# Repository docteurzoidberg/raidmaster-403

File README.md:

# Raidmaster 403

Tripmaster GPS de rallye-raid fait maison pour une **Peugeot 403 break Familiale de 1961**, pensé pour le raid
**Crazy Dust 2027** et utilisable au quotidien en mode balade. Boîtier autonome aimanté sur la tôle du
tableau de bord : distances partielles A et B, odomètre, vitesse, cap, moyenne, chrono.

Site du projet : **<https://docteurzoidberg.github.io/raidmaster-403/>** (présentation, maquette 3D, simulateur
dans le navigateur, manuel d'utilisation en cours de rédaction).

<p align="center"><sub>Simulateur PC, échelle 1:1 de l'écran 480 × 320. GIF régénéré automatiquement à chaque build qui change l'interface.</sub></p>

## Matériel

| Élément | Choix |
|---|---|
| Carte | [Waveshare ESP32-S3-Touch-LCD-3.5B](https://www.waveshare.com/wiki/ESP32-S3-Touch-LCD-3.5B) : ESP32-S3, 8 Mo PSRAM, 16 Mo flash |
| Écran | 3,5" IPS 480 × 320, AXS15231B en QSPI, tactile capacitif intégré |
| GPS | au choix au montage : u-blox NEO-M9N sur la carte fille (UART, 10 Hz) + antenne active déportée sous le pare-brise, ou module externe NEO-M8N + boussole (« puck » de drone) posé sur le tableau de bord |
| Cap | magnétomètre QMC5883L (I²C) |
| Alimentation | batterie Li-ion interne gérée par l'AXP2101, recharge USB-C, aucun fil 12 V |
| Commandes | 5 boutons (A, B, menu, ▲ haut / +, ▼ bas / −) + tactile |
| Boîtier | PETG / ASA imprimé (pas de PLA : habitacle à 60 °C en été) ; fixation sur la tôle à définir (plus d'aimants noyés dans le boîtier ; des aimants rapportés au dos restent possibles) |

Distance **GPS uniquement**, sans capteur de roue ni intervention sur le câblage de la voiture.

## État

| Étape | Contenu | État |
|---|---|---|
| 1 | Squelette CMake + simulateur SDL 480 × 320 | fait |
| 2 | Core portable + tests : `gps_parser` (NMEA, sur minmea), `trip_engine` (distance, moyenne, chrono, calibration), `app` (boutons, menu, sauvegarde) | fait |
| 3 | Interface LVGL câblée sur le core : raid, balade, menu réglages actif, calibration auto, démarrage animé, mode nuit | fait |
| 4 | Simulateur : rejeu de traces NMEA, trajet simulé, scénarios de bout en bout | 23 scénarios en place (GPS, puck débranché, calibration de la boussole) ; simulateur web dans le navigateur (WebAssembly, maquette 3D et carte) ; inclinomètre et matériel à venir |
| 5-6 | HAL ESP32 et firmware sur la carte | en cours : firmware de démo validé sur la carte (écran, tactile, core et UI du sim, trajet GPS simulé, NVS, heure de la RTC, état USB / batterie), jingle de démarrage par le codec ES8311 (à écouter sur la carte) ; pilote du récepteur GPS réel écrit (NEO-M9N ou puck NEO-M8N sur UART : débit trouvé, modèle reconnu, réglé à 10 Hz) et de sa boussole (QMC5883L, IST8310, HMC5883L ou LIS3MDL sur I²C, cap dans le journal), à essayer sur la carte ; cap à l'écran, boutons, charge de la batterie à venir |
| 7-13 | Essai en modules, carte fille 4 couches (GPS, magnétomètre), boîtier aimanté, essai raid | à faire ; carte 3.5B reçue, datasheets et modèle 3D rassemblés ; PCB placé, non routé (version 1.1 : GPS interne ou puck externe) ; maquette 3D des cartes dans un boîtier de principe validée ([en ligne](https://docteurzoidberg.github.io/raidmaster-403/mockup/)) ; boîtier dessiné dans Fusion, STEP des pièces dans `enclosure/stepfiles/`, à éprouver |

Pas encore là : compensation d'inclinaison de la boussole, réglages de charge de la batterie (l'état
USB / batterie est lu, pas configuré), température réelle, log GPX.

## Maquette 3D

Les trois cartes (Waveshare, carte fille GPS et magnétomètre, carte boutons) dans leur boîtier (aspect
retenu : cannelures, pare-chocs en TPU, liseré et lettrage), assemblé ou éclaté, à faire tourner dans le navigateur : **<https://docteurzoidberg.github.io/raidmaster-403/mockup/>**. Sources de la page
dans [`web/mockup/`](web/mockup/) ; modèles 3D externes et fichiers STEP du boîtier dessiné dans Fusion (pièces
à éprouver) dans [`enclosure/`](enclosure/README.md).

<p align="center"><sub>Rendus Blender de la maquette : boîtier de 123 × 94 × 33 mm avec l'aspect retenu, esquisse du modèle dessiné pour l'impression.</sub></p>

## Simulateur dans le navigateur

Le firmware (mêmes `core/` et `ui/`, compilés en WebAssembly) tourne dans la maquette 3D : l'écran est
vivant, les cinq capuchons se cliquent (appui long en gardant le doigt 0,6 s), et une carte OpenStreetMap
suit le trajet GPS rejoué : **<https://docteurzoidberg.github.io/raidmaster-403/sim/>** (menu de toutes les
pages du site). Trajets : les scénarios des tests, ou un fichier NMEA à glisser sur la page
(il reste dans le navigateur) ; vitesse ×1 à ×1000 ; la case « Jouer les actions et les vérifications »
rejoue les appuis du scénario et affiche ses vérifications en vert ou rouge. Trips et réglages restent dans
le navigateur (bouton « Remise à zéro »). Son coupé par défaut (bouton « Son »). Mêmes touches que le
simulateur PC. Le tripmaster s'affiche de face (bouton « Recentrer » après une rotation) ; le bouton « Écran
seul » montre l'écran sur toute la largeur, avec une barre des cinq boutons dessous (`?vue=2d` l'ouvre
directement). Sur la carte, « Centrer » garde le véhicule au centre (un glisser le coupe).

Construit en local et commité dans `web/sim/` (publié avec le site). Prérequis :
[emsdk](https://emscripten.org/docs/getting_started/downloads.html) installé dans `~/sdk/emsdk` (ou
`EMSDK_DIR`), Node (celui d'emsdk suffit).

```bash
cd software
tools/web.sh             # build (build-web/), test sous Node, copie dans web/sim/
tools/web.sh serve       # sert le site web/ : http://localhost:8000/ (accueil), …/sim/
```

`tools/web.sh build`, `test` et `copy` font chaque étape seule. Le test joue les 23 scénarios dans le
module WebAssembly avec leurs vérifications, et compare une capture de l'écran à celle du simulateur PC
(identique au pixel près).

## Cartes électroniques

Deux circuits fabriqués d'un seul tenant puis séparés : la **carte fille** (78 × 54 mm, 4 couches), enfichée
au dos de la Waveshare, existe en deux variantes choisies au soudage : **GPS interne** (NEO-M9N, prise
d'antenne U.FL et boussole) ou **puck externe** (prise JST-PH 6 broches au bord gauche, protection et tampon
I²C pour le branchement à chaud) ; la **carte boutons**
(108 × 20 mm), vissée derrière la façade, porte les 5 poussoirs, les 2 voyants et deux expandeurs I²C, et
rejoint la carte fille par une nappe souple de 6 voies. Tout se soude au fer.

<p align="center"><sub>Rendus du visualiseur 3D de KiCad, dessus (côté batterie) et dessous (côté écran) : composants placés, routage à venir.</sub></p>

## Démarrage rapide (simulateur PC)

Prérequis : CMake ≥ 3.20, Ninja, un compilateur C11, SDL2 (`sudo apt install libsdl2-dev` sous
Debian / Ubuntu / WSL). LVGL, Unity et les autres dépendances sont téléchargées par CMake ou déjà dans le
dépôt. Le code est dans `software/` : les commandes se lancent depuis ce dossier.

```bash
cd software
cmake --preset sim
cmake --build build-sim
./build-sim/raidmaster-sim                                    # trajet simulé
./build-sim/raidmaster-sim --replay trace.nmea --speed 10     # rejoue un fichier NMEA ×10
```

Le core tourne comme sur la carte : GPS fourni par le simulateur (trajet simulé ou fichier rejoué),
réglages et distances sauvegardés dans `sim-storage.json`. Au lancement, le jingle de démarrage se joue
avec l'animation par la sortie audio SDL (WSLg sous WSL) ; `SDL_AUDIODRIVER=dummy` le coupe.

| Option | Effet |
|---|---|
| `--replay fichier.nmea` | rejoue un fichier au rythme de ses horodatages (sinon trajet simulé : boucle de 2 min) |
| `--speed N` | accélère le temps GPS, 1 à 1000 |
| `--loop` | rejoue le fichier en boucle |
| `--storage f.json` / `--no-storage` | fichier de sauvegarde (défaut `./sim-storage.json`) / en mémoire |
| `--script actions.txt --out dossier` | joue des actions horodatées en temps virtuel, sans attente (tests de bout en bout) |

| Touche | Bouton / action |
|---|---|
| `a` / `b` | A / B : RAZ Trip A / Trip B ; à la calibration auto : départ et arrivée (A), annuler (B) |
| `+` / `−` | ±10 m sur le trip actif ; dans le menu : monter / descendre, ou changer la valeur en édition |
| `m` | trip actif A ↔ B ; dans le menu : choisir / valider |
| `Maj` + touche | appui long : `Maj`+`m` entre dans le menu ou en sort, `Maj`+`+`/`−` ±100 m |
| `n` ou `Tab` | bascule jour / nuit |
| `d` | coupe / rétablit le signal GPS (tunnel) |
| `g` | débranche / rebranche le récepteur GPS (« GPS × », puis recherche du débit et réglage) |
| `c` | débranche / rebranche la boussole |
| `r` | la voiture tourne sur place / s'arrête (calibration de la boussole) |
| `p` | alimentation suivante (barre d'état) : batterie 68 %, USB en charge, USB batterie pleine, USB sans batterie, batterie 8 % |
| `v` | écran suivant (debug) |
| `Échap` | quitter (sauvegarde) |

### Tests

```bash
cd software
ctest --preset sim
tools/check.sh        # build + avertissements + tests + GIF + build firmware + simulateur web, résumé court
                      # (-c : tout recompiler, -s : sim seul, -w : sans le web)
```

- Tests unitaires du core avec [Unity](https://github.com/ThrowTheSwitch/Unity) : parseur NMEA, moteur
  de distance, application (boutons, menu, sauvegarde, source du cap), liaison avec le récepteur u-blox,
  boussole, synthétiseur et jingle de démarrage.
- Scénarios de bout en bout (`software/tests/fixtures/scenarios/`, 23 au catalogue) : le simulateur sans fenêtre
  rejoue une trace, appuie sur les boutons et vérifie l'état, en temps virtuel (une étape de 12 h se
  joue en moins d'une seconde, la suite entière en ~1,5 s). Les traces sont générées au build depuis
  l'itinéraire `route.txt` de chaque scénario (`software/tests/tools/gen_route.py`, Python sans dépendance).
- Les traces NMEA longues de `software/references/traces-brutes/` ne sont pas versionnées : présentes, elles sont
  rejouées (distances à ±0,1 % de la référence) ; absentes, ces tests sont ignorés.

### GIF de démo

`docs/demo/raidmaster-demo.gif` est régénéré par la cible CMake `demo_gif` à chaque build où le binaire du
simulateur change. Le simulateur tourne alors sans fenêtre, en temps virtuel, et enchaîne démarrage, raid,
balade, menu, calibration et raid de nuit. Le GIF se commite avec la modification d'interface qui l'a
produit.

- Désactiver : `cmake --preset sim -DRAIDMASTER_DEMO_GIF=OFF`.
- À la demande, agrandi ou vers un autre fichier : `software/tools/demo_gif.sh [-s 1..4] [-o sortie.gif]`.

### Animation de démarrage

La 403 fait un tour sur une grille cyan lumineuse, calé sur le jingle : elle s'élance sur les arpèges
puis ralentit en roue libre et s'arrête avec la fin de l'accord. L'animation est rendue dans **Blender**
(36 images en 480 × 320), puis convertie au build en `boot_anim.bin` (palette 256 couleurs) par
`ui/assets/boot_anim/build_boot_anim.py`. Deux formats, mêmes pixels, à trancher : **2** par défaut
(chaque image codée par différence avec la précédente, 0,95 Mo) ou **1** (images brutes, 5,5 Mo), choisi
par l'option CMake `RAIDMASTER_BOOT_ANIM_FORMAT`. Cette conversion demande Python avec Pillow et numpy,
désigné par la variable CMake `RAIDMASTER_PYTHON`.

La scène Blender et les images rendues ne sont pas publiées : elles reposent sur un modèle 3D de la 403
sous licence. Sans elles, ou sans Python, le build passe et l'écran de démarrage affiche une silhouette
fixe.

### Son

Le jingle de démarrage « Grille néon » (arpèges la m · fa · sol puis accord de La majeur, ~2,9 s) est
synthétisé à la volée par `core/synth.c` à partir d'une table de notes (`core/jingles.c`), en PCM 16 bits
mono à 22 050 Hz, sans fichier audio. Sortie SDL sur le sim, codec ES8311 et ampli NS4150B sur la carte
(volume dans `tools/fw.sh menuconfig`).

### Version

Le numéro de version est dans `software/VERSION` (seule source). L'écran de démarrage l'affiche avec la
plateforme : `v0.1.0 · SIM` sur le sim, `v0.1.0 · ESP32 · fe63e9e` sur la carte (hash git du firmware,
suivi de `*` s'il a été compilé avec des modifications non commitées). ESP-IDF reprend le même numéro.

### Polices

Tout l'affichage est en **Share Tech Mono**, compilée en polices bitmap LVGL, uniquement pour les tailles
et les glyphes utilisés. Les mêmes fichiers servent au simulateur et à l'ESP32. Régénération :
`ui/fonts/gen_fonts.sh` (demande Node.js, appelle `lv_font_conv`).

## Participer au projet : partir de zéro

Le développement se fait sur PC, sans la carte : simulateur et tests suffisent jusqu'à l'étape 5.
Testé sous Ubuntu 24.04 (natif ou WSL2).

1. **Outils système**

   ```bash
   sudo apt install build-essential cmake ninja-build git pkg-config libsdl2-dev python3-venv
   ```

   CMake ≥ 3.20. Sous WSL2, la fenêtre SDL s'affiche via WSLg (Windows 11).

2. **Cloner**

   ```bash
   git clone git@github.com:docteurzoidberg/raidmaster-403.git
   cd raidmaster-403
   ```

3. **Python + Pillow + numpy** (optionnel, pour l'animation de démarrage)

   ```bash
   python3 -m venv .venv
   .venv/bin/pip install pillow numpy
   ```

   CMake prend `.venv/` à la racine du dépôt (à côté de `software/`) s'il existe, sinon le `python3` du système. Pour en
   imposer un autre : `-DRAIDMASTER_PYTHON=/chemin/vers/python`. Sans Pillow ou numpy, le build passe
   quand même : le démarrage affiche une silhouette fixe.

4. **Configurer, compiler, tester, lancer**

   ```bash
   cd software
   cmake --preset sim          # télécharge LVGL et Unity au premier passage (connexion requise)
   cmake --build build-sim
   ctest --preset sim
   ./build-sim/raidmaster-sim
   ```

   Le build régénère aussi `docs/demo/raidmaster-demo.gif`. Si tu ne touches pas à l'interface et que
   `git status` le montre modifié, annule-le (`git checkout docs/demo/raidmaster-demo.gif`) ou configure
   avec `-DRAIDMASTER_DEMO_GIF=OFF`.

5. **Traces NMEA de test** (optionnel). `software/references/` n'est pas versionné. Les traces longues se
   génèrent avec les scripts Python de `software/tests/tools/` (sans dépendance, voir `software/tests/tools/README.md`),
   par exemple :

   ```bash
   mkdir -p software/references/traces-brutes
   python3 software/tests/tools/gen_nmea.py --mode linear --duration 3600 --rate 10 --speed-kmh 90 \
       --heading-deg 90 --start-lat 48.8566 --start-lon 2.3522 --start-utc 2026-10-09T06:00:00+00:00 \
       --out software/references/traces-brutes/stage_highway_1h.nmea
   ```

   Sans elles, les tests qui les rejouent sont ignorés. Si les paramètres diffèrent de ceux de
   référence, ces tests peuvent échouer sur les comptes attendus.

6. **Avant de proposer une modification**
   - Pour un changement important, ouvrir d'abord une issue pour en discuter.
   - C11 strict, compilation sans avertissement (`-Wall -Wextra -Wpedantic`), `core/` sans aucun
     accès matériel ni LVGL.
   - Une branche par sujet, `software/tools/check.sh` propre (aucun avertissement, tests verts), GIF de démo commité avec toute modification de
     l'interface, ce README mis à jour s'il devient faux.
   - Optionnel : `compile_commands.json` est exporté dans `software/build-sim/` pour clangd ou ton IDE (lien
     symbolique à la racine si besoin).
   - Code sous GPL-3.0.

## Firmware ESP32

Projet ESP-IDF dans `software/firmware/`, construit avec **ESP-IDF v5.5.6** et les **mêmes** `core/` et
`ui/` que le simulateur (leurs `CMakeLists.txt` servent aux deux builds) ; les pilotes de la carte sont
dans `software/hal_esp32/`. Version actuelle : **démo** sans périphérique externe (trajet GPS simulé,
tactile en guise de boutons, sauvegarde en NVS, animation de démarrage en flash, jingle de démarrage par
le codec ES8311, heure de la RTC, état USB / batterie lu sur le PMIC).

```bash
cd software
tools/fw.sh build        # compile (ESP-IDF chargé par le script)
tools/fw.sh flash        # programme + animation de démarrage, puis 10 s de journal de la carte
tools/fw.sh log 20       # redémarre la carte et affiche 20 s de journal
tools/fw.sh menuconfig   # menu « Raidmaster 403 » : sens de l'écran, rétroéclairage, volume, tactile-boutons, source GPS, boussole
```

Installation d'ESP-IDF, liaison de la carte à WSL (usbipd), réglages et dépannage :
[`software/firmware/README.md`](software/firmware/README.md).

## Organisation du dépôt

```
software/        tout le code ; CMakeLists.txt et CMakePresets.json, build dans software/build-sim/ ;
                 VERSION : numéro de version
  core/          logique métier en C11 portable (aucun accès matériel) : gps_parser, trip_engine, app,
                 gps_synth (trajet simulé), ubx et gps_link (liaison avec un récepteur u-blox), mag (boussole),
                 synth et jingles (son) ; core/include/hal/ : interfaces matériel ;
                 core/third_party/minmea
  ui/            interface LVGL v9 : écrans, thème jour / nuit, polices, images, animation de démarrage
  sim/           simulateur PC SDL2 : fenêtre, clavier, options, mode script (script.c), captures, GIF
  hal_sim/       HAL du simulateur : GPS (rejeu, trajet simulé), stockage JSON, horloge, assets, son SDL
  simweb/        simulateur web (WebAssembly) : front-end, index des scénarios, test Node (tests/)
  hal_simweb/    HAL du simulateur web : stockage du navigateur, son Web Audio (le reste vient de hal_sim/)
  hal_esp32/     HAL et pilotes de la carte (écran QSPI, tactile, RTC, PMIC, son ES8311, NVS, GPS de démo ou réel…),
                 composant ESP-IDF
  firmware/      projet ESP-IDF (main/, sdkconfig.defaults, partitions.csv), build dans software/build-firmware/
  cmake/         modules CMake communs au sim et au firmware (animation de démarrage, version)
  tests/         tests unitaires Unity, scénarios (fixtures/scenarios/), tools/ : outils Python NMEA
  tools/         scripts : check.sh (vérification complète), fw.sh (firmware), web.sh (simulateur web), demo_gif.sh
  references/    non versionné : traces NMEA de test
hardware/kicad/carte-fille/
                 projet KiCad 10 de la carte fille et de la carte boutons (schémas, PCB, bibliothèques,
                 3d/ : modèles 3D propres et leur provenance, export/ : STEP des deux cartes)
hardware/kicad/BOM.md
                 composants des deux cartes : version GPS intégré et version puck GPS externe
enclosure/       boîtier : modèles 3D externes utilisés (README.md), stepfiles/ : exports STEP des pièces du boîtier
web/             site publié sur GitHub Pages : accueil (index.html), common/ : en-tête et styles communs,
                 mockup/ : maquette 3D des cartes dans leur boîtier (page three.js et modèle GLB),
                 sim/ : simulateur web (page, module construit par tools/web.sh, scénarios),
                 manual/ : manuel d'utilisation (en cours de rédaction), img/ : images de l'accueil
.github/         workflow de publication de web/ sur GitHub Pages
docs/demo/       GIF de démo, rendus des cartes (KiCad) et du boîtier (Blender)
```

## Documentation

- [`software/firmware/README.md`](software/firmware/README.md) : installation d'ESP-IDF, liaison de la
  carte, réglages et dépannage du firmware.
- [`software/tests/tools/README.md`](software/tests/tools/README.md) : outils NMEA (génération, bruit,
  validation, enregistrement).
- [`software/tests/fixtures/scenarios/README.md`](software/tests/fixtures/scenarios/README.md) : catalogue
  des scénarios de bout en bout.
- [`enclosure/README.md`](enclosure/README.md) : modèles 3D externes et fichiers STEP du boîtier.
- [`web/README.md`](web/README.md) : le site ([en ligne](https://docteurzoidberg.github.io/raidmaster-403/)) :
  accueil, maquette 3D, simulateur web, manuel.

## Licence

[GPL-3.0](LICENSE).

Composants tiers :

| Composant | Licence | Usage |
|---|---|---|
| [LVGL](https://lvgl.io) v9.2.2 | MIT | interface, téléchargé au build (FetchContent pour le sim, registre ESP-IDF pour le firmware) |
| [ESP-IDF](https://github.com/espressif/esp-idf) v5.5.6 | Apache-2.0 | framework du firmware, installé à part |
| [esp_lcd_axs15231b](https://components.espressif.com/components/espressif/esp_lcd_axs15231b) 1.0.1, [esp_io_expander_tca9554](https://components.espressif.com/components/espressif/esp_io_expander_tca9554) 2.0.3 | Apache-2.0 | pilotes d'écran et d'expandeur, téléchargés au build |
| [esp_codec_dev](https://components.espressif.com/components/espressif/esp_codec_dev) 1.3.4 | Apache-2.0 | pilote du codec audio ES8311, téléchargé au build |
| Séquence d'init du panneau ([exemples Waveshare](https://github.com/waveshareteam/ESP32-S3-Touch-LCD-3.5B)) | Apache-2.0 | dans `hal_esp32/board_display.c` |
| [minmea](https://github.com/kosma/minmea) | MIT (au choix WTFPL / MIT / LGPL-3) | décodage NMEA, dans `core/third_party/minmea/` |
| [Unity](https://github.com/ThrowTheSwitch/Unity) v2.6.1 | MIT | tests, téléchargé au build |
| [Share Tech Mono](https://fonts.google.com/specimen/Share+Tech+Mono) | SIL OFL 1.1 | police, dans `ui/assets/` |
| [three.js](https://threejs.org) 0.186.1 | MIT | maquette 3D et simulateur web (`web/`), chargé depuis jsDelivr |
| [Leaflet](https://leafletjs.com) 1.9.4 | BSD-2-Clause | carte du simulateur web (`web/sim/`), chargé depuis jsDelivr |
| Tuiles [OpenStreetMap](https://www.openstreetmap.org/copyright) | données ODbL, attribution affichée | fond de carte du simulateur web, usage léger ([politique des tuiles](https://operations.osmfoundation.org/policies/tiles/)) |
| [Emscripten](https://emscripten.org) | MIT / University of Illinois NCSA | compilateur du simulateur web, installé à part ; son code d'exécution est dans le module construit |

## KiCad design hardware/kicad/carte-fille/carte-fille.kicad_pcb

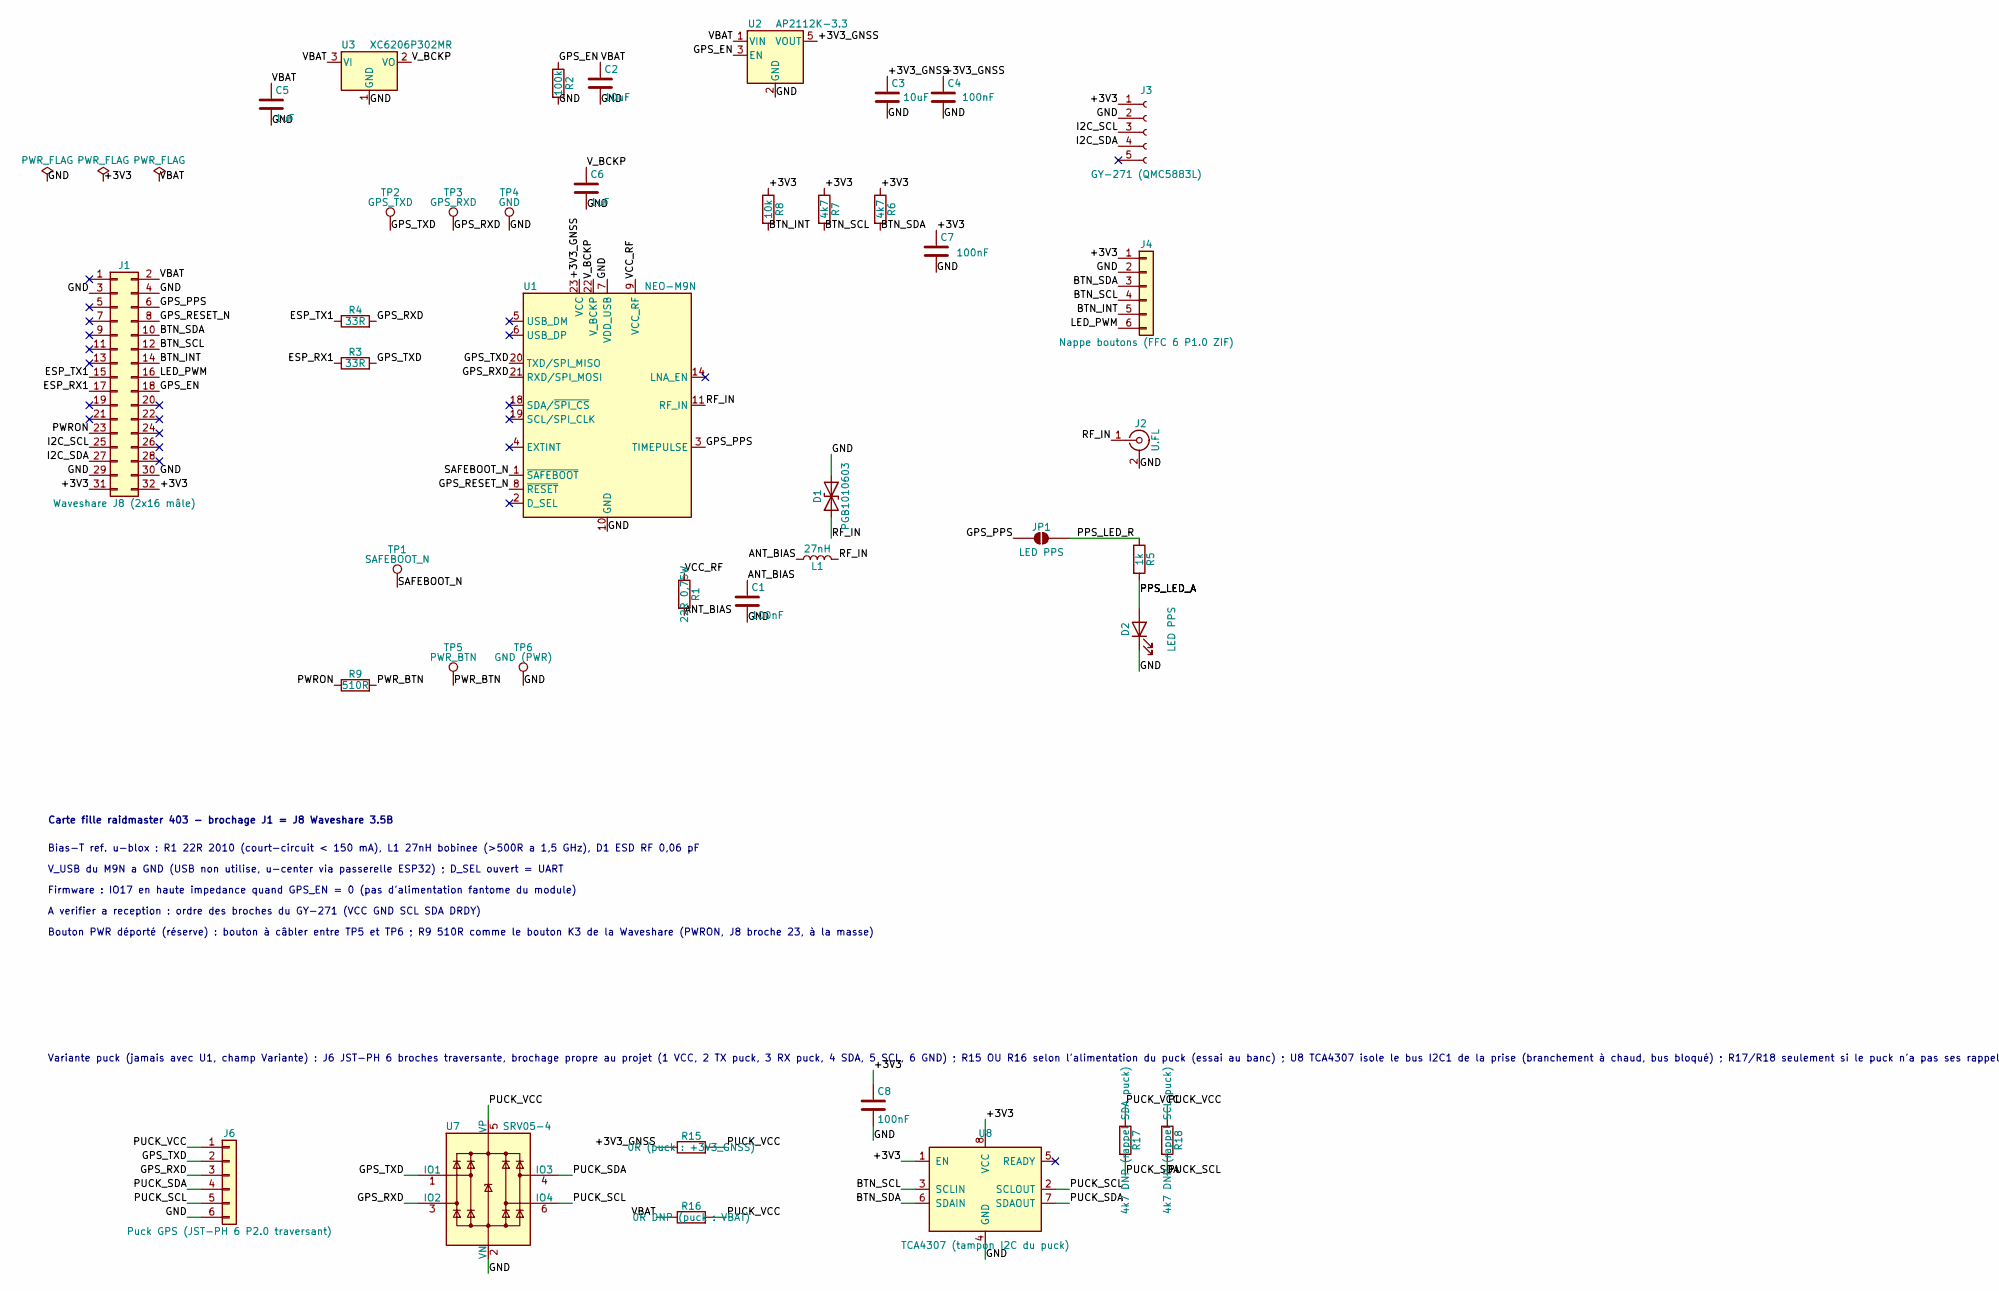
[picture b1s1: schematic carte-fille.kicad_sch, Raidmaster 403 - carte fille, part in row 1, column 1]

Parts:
C1, C4, C7, C8: 100nF; C_0805_2012Metric_Pad1.18x1.45mm_HandSolder
C2, C3: 10uF; C_0805_2012Metric_Pad1.18x1.45mm_HandSolder
C5, C6: 1uF; C_0805_2012Metric_Pad1.18x1.45mm_HandSolder
D1: PGB1010603; D_0603_1608Metric_Pad1.05x0.95mm_HandSolder
D2: LED PPS; LED_0805_2012Metric_Pad1.15x1.40mm_HandSolder
J1: Waveshare J8 (2x16 mâle); PinHeader_2x16_P2.54mm_Vertical
J2: U.FL; U.FL_Hirose_U.FL-R-SMT-1_Vertical
J3: GY-271 (QMC5883L); PinHeader_1x05_P2.54mm_Vertical
J4: Nappe boutons (FFC 6 P1.0 ZIF); TE_84952-6_1x06-1MP_P1.0mm_Horizontal
J6: Puck GPS (JST-PH 6 P2.0 traversant); JST_PH_S6B-PH-K_1x06_P2.00mm_Horizontal
JP1: LED PPS; SolderJumper-2_P1.3mm_Open_RoundedPad1.0x1.5mm
L1: 27nH; L_0805_2012Metric_Pad1.05x1.20mm_HandSolder
R1: 22R 0,75W; R_2010_5025Metric_Pad1.40x2.65mm_HandSolder
R2: 100k; R_0805_2012Metric_Pad1.20x1.40mm_HandSolder
R3, R4: 33R; R_0805_2012Metric_Pad1.20x1.40mm_HandSolder
R5: 1k; R_0805_2012Metric_Pad1.20x1.40mm_HandSolder
R6, R7: 4k7; R_0805_2012Metric_Pad1.20x1.40mm_HandSolder
R8: 10k; R_0805_2012Metric_Pad1.20x1.40mm_HandSolder
R9: 510R; R_0805_2012Metric_Pad1.20x1.40mm_HandSolder
R15: 0R (puck : +3V3_GNSS); R_0805_2012Metric_Pad1.20x1.40mm_HandSolder
R16: 0R DNP (puck : VBAT); R_0805_2012Metric_Pad1.20x1.40mm_HandSolder
R17: 4k7 DNP (rappel SDA puck); R_0805_2012Metric_Pad1.20x1.40mm_HandSolder
R18: 4k7 DNP (rappel SCL puck); R_0805_2012Metric_Pad1.20x1.40mm_HandSolder
TP1: SAFEBOOT_N; TestPoint_Pad_D1.5mm
TP2: GPS_TXD; TestPoint_Pad_D1.5mm
TP3: GPS_RXD; TestPoint_Pad_D1.5mm
TP4: GND; TestPoint_Pad_D1.5mm
TP5: PWR_BTN; TestPoint_Pad_D2.0mm
TP6: GND (PWR); TestPoint_Pad_D2.0mm
U1: NEO-M9N; ublox_NEO
U2: AP2112K-3.3; SOT-23-5_HandSoldering
U3: XC6206P302MR; SOT-23_Handsoldering
U7: SRV05-4; SOT-23-6_Handsoldering
U8: TCA4307 (tampon I2C du puck); VSSOP-8_3x3mm_P0.65mm

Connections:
/+3V3: C7.1, C8.1, J1.31, J1.32, J3.1, J4.1, R6.1, R7.1, R8.1, U8.1 (EN), U8.8 (VCC)
/+3V3_GNSS: C3.1, C4.1, R15.1, U1.23 (VCC), U2.5 (VOUT)
/ANT_BIAS: C1.1, L1.1, R1.2
/BTN_INT: J1.14, J4.5, R8.2
/BTN_SCL: J1.12, J4.4, R7.2, U8.3 (SCLIN)
/BTN_SDA: J1.10, J4.3, R6.2, U8.6 (SDAIN)
/ESP_RX1: J1.17, R3.1
/ESP_TX1: J1.15, R4.1
/GND: C1.2, C2.2, C3.2, C4.2, C5.2, C6.2, C7.2, C8.2, D1.2 (A2), D2.1 (K), J1.3, J1.4, J1.29, J1.30, J2.2 (Ext), J3.2, J4.2, J6.6, R2.2, TP4.1 (1_1), TP6.1 (1_1), U1.7 (VDD_USB), U1.10 (GND), U1.12 (GND), U1.13 (GND), U1.24 (GND), U2.2 (GND), U3.1 (GND), U7.2 (VN), U8.4 (GND)
/GPS_EN: J1.18, R2.1, U2.3 (EN)
/GPS_PPS: J1.6, JP1.1 (A), U1.3 (TIMEPULSE)
/GPS_RESET_N: J1.8, U1.8 (~RESET)
/GPS_RXD: J6.3, R4.2, TP3.1 (1_1), U1.21 (RXD/SPI_MOSI), U7.3 (IO2)
/GPS_TXD: J6.2, R3.2, TP2.1 (1_1), U1.20 (TXD/SPI_MISO), U7.1 (IO1)
/I2C_SCL: J1.25, J3.3
/I2C_SDA: J1.27, J3.4
/LED_PWM: J1.16, J4.6
/PPS_LED_A: D2.2 (A), R5.2
/PPS_LED_R: JP1.2 (B), R5.1
/PUCK_SCL: J6.5, R18.2, U7.6 (IO4), U8.2 (SCLOUT)
/PUCK_SDA: J6.4, R17.2, U7.4 (IO3), U8.7 (SDAOUT)
/PUCK_VCC: J6.1, R15.2, R16.2, R17.1, R18.1, U7.5 (VP)
/PWRON: J1.23, R9.1
/PWR_BTN: R9.2, TP5.1 (1_1)
/RF_IN: D1.1 (A1), J2.1 (In), L1.2, U1.11 (RF_IN)
/SAFEBOOT_N: TP1.1 (1_1), U1.1 (~SAFEBOOT)
/VBAT: C2.1, C5.1, J1.2, R16.1, U2.1 (VIN), U3.3 (VI)
/VCC_RF: R1.1, U1.9 (VCC_RF)
/V_BCKP: C6.1, U1.22 (V_BCKP), U3.2 (VO)

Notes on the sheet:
Bouton PWR déporté (réserve) : bouton à câbler entre TP5 et TP6 ; R9 510R comme le bouton K3 de la Waveshare (PWRON, J8 broche 23, à la masse)
V_USB du M9N a GND (USB non utilise, u-center via passerelle ESP32) ; D_SEL ouvert = UART
A verifier a reception : ordre des broches du GY-271 (VCC GND SCL SDA DRDY)
Carte fille raidmaster 403 - brochage J1 = J8 Waveshare 3.5B
2 × PCF8574T sur bus I2C1 dédié (100 kHz max) : U102 = boutons, 0x20, P0-P4 = BTN1-BTN5, INT ; U103 = LED, 0x21, P0-P3 = cathodes ; P5-P7 / P4-P7 en réserve
A verifier a reception : brochage KAK (anode au milieu) et couleur de K1 / K2 des LED bicolores
Bias-T ref. u-blox : R1 22R 2010 (court-circuit < 150 mA), L1 27nH bobinee (>500R a 1,5 GHz), D1 ESD RF 0,06 pF
LED_PWM actif bas (P-MOSFET Q101) : PWM IO42 = luminosité globale ; sortie de U103 à 0 = couleur allumée (cathode tirée à la masse)
Partie détachable (mouse bites) : nets F_* séparés de la carte fille, reliés seulement par la nappe FFC 6 voies
Variante puck (jamais avec U1, champ Variante) : J6 JST-PH 6 broches traversante, brochage propre au projet (1 VCC, 2 TX puck, 3 RX puck, 4 SDA, 5 SCL, 6 GND) ; R15 OU R16 selon l'alimentation du puck (essai au banc) ; U8 TCA4307 isole le bus I2C1 de la prise (branchement à chaud, bus bloqué) ; R17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
Firmware : IO17 en haute impedance quand GPS_EN = 0 (pas d'alimentation fantome du module)

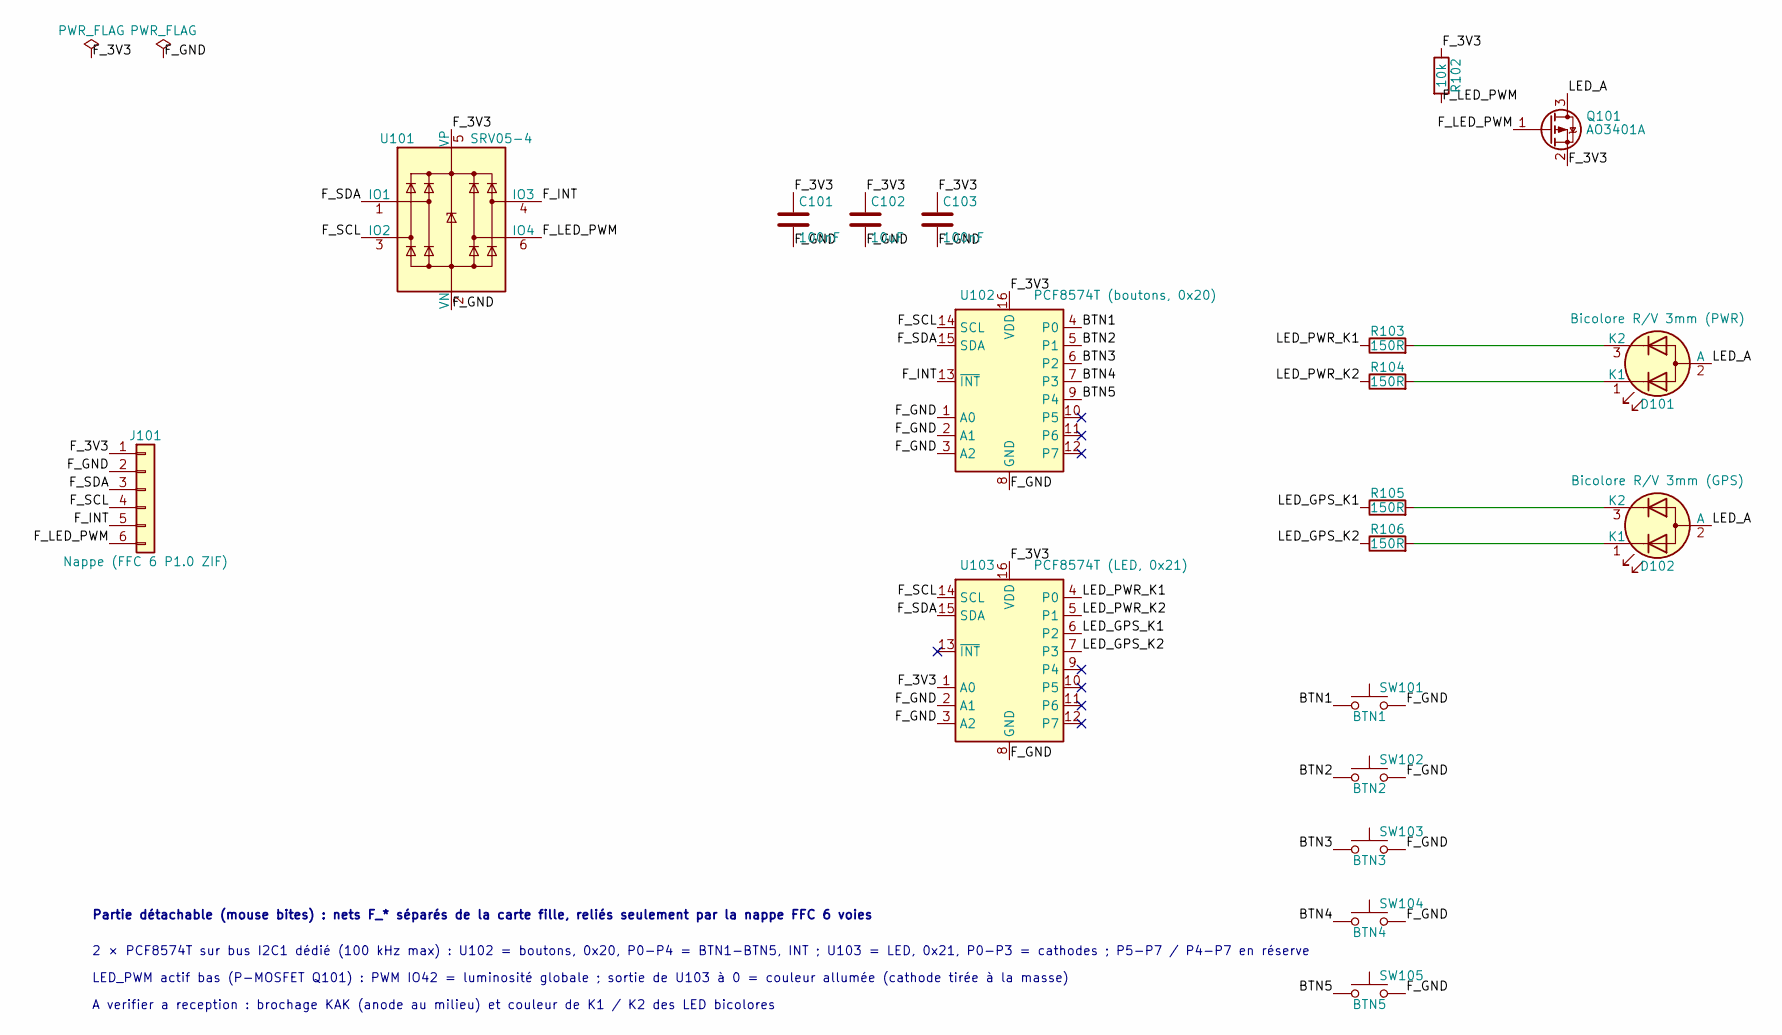
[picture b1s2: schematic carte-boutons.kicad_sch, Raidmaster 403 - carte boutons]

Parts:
C101, C103: 100nF; C_0805_2012Metric_Pad1.18x1.45mm_HandSolder
C102: 10uF; C_0805_2012Metric_Pad1.18x1.45mm_HandSolder
D101: Bicolore R/V 3mm (PWR); LED_D3.0mm-3
D102: Bicolore R/V 3mm (GPS); LED_D3.0mm-3
J101: Nappe (FFC 6 P1.0 ZIF); TE_84952-6_1x06-1MP_P1.0mm_Horizontal
Q101: AO3401A; SOT-23_Handsoldering
R102: 10k; R_0805_2012Metric_Pad1.20x1.40mm_HandSolder
R103, R104, R105, R106: 150R; R_0805_2012Metric_Pad1.20x1.40mm_HandSolder
SW101: BTN1; SW_PUSH-12mm
SW102: BTN2; SW_PUSH-12mm
SW103: BTN3; SW_PUSH-12mm
SW104: BTN4; SW_PUSH-12mm
SW105: BTN5; SW_PUSH-12mm
U101: SRV05-4; SOT-23-6_Handsoldering
U102: PCF8574T (boutons, 0x20); SOIC-16W_7.5x10.3mm_P1.27mm
U103: PCF8574T (LED, 0x21); SOIC-16W_7.5x10.3mm_P1.27mm

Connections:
/carte-boutons (partie détachable)/BTN1: SW101.1, U102.4 (P0)
/carte-boutons (partie détachable)/BTN2: SW102.1, U102.5 (P1)
/carte-boutons (partie détachable)/BTN3: SW103.1, U102.6 (P2)
/carte-boutons (partie détachable)/BTN4: SW104.1, U102.7 (P3)
/carte-boutons (partie détachable)/BTN5: SW105.1, U102.9 (P4)
/carte-boutons (partie détachable)/F_3V3: C101.1, C102.1, C103.1, J101.1, Q101.2 (S), R102.1, U101.5 (VP), U102.16 (VDD), U103.1 (A0), U103.16 (VDD)
/carte-boutons (partie détachable)/F_GND: C101.2, C102.2, C103.2, J101.2, SW101.2, SW102.2, SW103.2, SW104.2, SW105.2, U101.2 (VN), U102.1 (A0), U102.2 (A1), U102.3 (A2), U102.8 (GND), U103.2 (A1), U103.3 (A2), U103.8 (GND)
/carte-boutons (partie détachable)/F_INT: J101.5, U101.4 (IO3), U102.13 (~INT)
/carte-boutons (partie détachable)/F_LED_PWM: J101.6, Q101.1 (G), R102.2, U101.6 (IO4)
/carte-boutons (partie détachable)/F_SCL: J101.4, U101.3 (IO2), U102.14 (SCL), U103.14 (SCL)
/carte-boutons (partie détachable)/F_SDA: J101.3, U101.1 (IO1), U102.15 (SDA), U103.15 (SDA)
/carte-boutons (partie détachable)/LED_A: D101.2 (A), D102.2 (A), Q101.3 (D)
/carte-boutons (partie détachable)/LED_GPS_K1: R105.1, U103.6 (P2)
/carte-boutons (partie détachable)/LED_GPS_K2: R106.1, U103.7 (P3)
/carte-boutons (partie détachable)/LED_PWR_K1: R103.1, U103.4 (P0)
/carte-boutons (partie détachable)/LED_PWR_K2: R104.1, U103.5 (P1)
unnamed: D101.1 (K1), R104.2
unnamed: D101.3 (K2), R103.2
unnamed: D102.1 (K1), R106.2
unnamed: D102.3 (K2), R105.2

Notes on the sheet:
LED_PWM actif bas (P-MOSFET Q101) : PWM IO42 = luminosité globale ; sortie de U103 à 0 = couleur allumée (cathode tirée à la masse)
Partie détachable (mouse bites) : nets F_* séparés de la carte fille, reliés seulement par la nappe FFC 6 voies
2 × PCF8574T sur bus I2C1 dédié (100 kHz max) : U102 = boutons, 0x20, P0-P4 = BTN1-BTN5, INT ; U103 = LED, 0x21, P0-P3 = cathodes ; P5-P7 / P4-P7 en réserve
A verifier a reception : brochage KAK (anode au milieu) et couleur de K1 / K2 des LED bicolores

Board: 4 copper layers, 70 parts (11 on the bottom side), 49 nets, no tracks yet.

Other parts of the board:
CT1: Contour_carte_boutons
H1, H2, H3, H4, H5, H6, H7, H8: MountingHole_2.2mm_M2

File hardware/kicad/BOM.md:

# BOM des cartes du raidmaster 403

Composants des deux cartes (carte fille, carte boutons), lus dans les schémas KiCad de
`carte-fille/` : **fichier généré, ne pas modifier à la main** en dehors du bloc « Hors schéma ».
La section d'un composant vient de son champ `Variante` (`commun`, `interne`,
`puck`) ; la carte boutons est commune aux deux versions. Non monté = attribut DNP, hors BOM ou
« DNP » dans la valeur.

<!-- sources : `carte-fille.kicad_sch` 2e0da2376db3, `carte-boutons.kicad_sch` c4587fbc4d48 -->

## Version GPS intégré (NEO-M9N sur la carte fille)

### Carte fille (26 composants)

| Qté | Repères | Type | Valeur | Boîtier | Rôle |
|---:|---|---|---|---|---|
| 3 | C1, C4, C7 | Condensateur | 100nF | 0805 |  |
| 2 | C2, C3 | Condensateur | 10uF | 0805 |  |
| 2 | C5, C6 | Condensateur | 1uF | 0805 |  |
| 1 | R1 | Résistance | 22R 0,75W | 2010 |  |
| 1 | R2 | Résistance | 100k | 0805 |  |
| 2 | R3, R4 | Résistance | 33R | 0805 |  |
| 1 | R5 | Résistance | 1k | 0805 |  |
| 2 | R6, R7 | Résistance | 4k7 | 0805 |  |
| 1 | R8 | Résistance | 10k | 0805 |  |
| 1 | R9 | Résistance | 510R | 0805 |  |
| 1 | L1 | Inductance | 27nH | 0805 |  |
| 1 | D1 | Diode / LED | PGB1010603 | 0603 |  |
| 1 | D2 | Diode / LED | LED PPS | 0805 |  |
| 1 | J1 | Connecteur | Waveshare J8 | PinHeader_2x16_P2.54mm_Vertical | 2x16 mâle |
| 1 | J2 | Connecteur | U.FL | U.FL_Hirose_U.FL-R-SMT-1_Vertical |  |
| 1 | J3 | Connecteur | GY-271 | PinHeader_1x05_P2.54mm_Vertical | QMC5883L |
| 1 | J4 | Connecteur | Nappe boutons | TE_84952-6_1x06-1MP_P1.0mm_Horizontal | FFC 6 P1.0 ZIF |
| 1 | U1 | Circuit intégré | NEO-M9N | ublox_NEO |  |
| 1 | U2 | Circuit intégré | AP2112K-3.3 | SOT-23-5 |  |
| 1 | U3 | Circuit intégré | XC6206P302MR | SOT-23 |  |

Pastilles du PCB, rien à acheter : JP1, TP1, TP2, TP3, TP4, TP5, TP6.

### Carte boutons (20 composants)

| Qté | Repères | Type | Valeur | Boîtier | Rôle |
|---:|---|---|---|---|---|
| 5 | SW101, SW102, SW103, SW104, SW105 | Bouton | Poussoir 12 × 12 | SW_PUSH-12mm | SW101 : BTN1 ; SW102 : BTN2 ; SW103 : BTN3 ; SW104 : BTN4 ; SW105 : BTN5 |
| 2 | C101, C103 | Condensateur | 100nF | 0805 |  |
| 1 | C102 | Condensateur | 10uF | 0805 |  |
| 1 | R102 | Résistance | 10k | 0805 |  |
| 4 | R103, R104, R105, R106 | Résistance | 150R | 0805 |  |
| 2 | D101, D102 | Diode / LED | Bicolore R/V 3mm | LED_D3.0mm-3 | D101 : PWR ; D102 : GPS |
| 1 | J101 | Connecteur | Nappe | TE_84952-6_1x06-1MP_P1.0mm_Horizontal | FFC 6 P1.0 ZIF |
| 1 | Q101 | Transistor | AO3401A | SOT-23 |  |
| 1 | U101 | Circuit intégré | SRV05-4 | SOT-23-6 |  |
| 2 | U102, U103 | Circuit intégré | PCF8574T | SOIC-16W_7.5x10.3mm_P1.27mm | U102 : boutons, 0x20 ; U103 : LED, 0x21 |

**Total : 46 composants à souder.**

## Version puck GPS externe (composants minimaux)

### Carte fille (20 composants)

| Qté | Repères | Type | Valeur | Boîtier | Rôle |
|---:|---|---|---|---|---|
| 2 | C2, C3 | Condensateur | 10uF | 0805 |  |
| 3 | C4, C7, C8 | Condensateur | 100nF | 0805 |  |
| 1 | R2 | Résistance | 100k | 0805 |  |
| 2 | R3, R4 | Résistance | 33R | 0805 |  |
| 2 | R6, R7 | Résistance | 4k7 | 0805 |  |
| 1 | R8 | Résistance | 10k | 0805 |  |
| 1 | R9 | Résistance | 510R | 0805 |  |
| 1 | R15 | Résistance | 0R | 0805 | puck : +3V3_GNSS |
| 1 | J1 | Connecteur | Waveshare J8 | PinHeader_2x16_P2.54mm_Vertical | 2x16 mâle |
| 1 | J3 | Connecteur | GY-271 | PinHeader_1x05_P2.54mm_Vertical | QMC5883L |
| 1 | J4 | Connecteur | Nappe boutons | TE_84952-6_1x06-1MP_P1.0mm_Horizontal | FFC 6 P1.0 ZIF |
| 1 | J6 | Connecteur | Puck GPS | JST_PH_S6B-PH-K_1x06_P2.00mm_Horizontal | JST-PH 6 P2.0 traversant |
| 1 | U2 | Circuit intégré | AP2112K-3.3 | SOT-23-5 |  |
| 1 | U7 | Circuit intégré | SRV05-4 | SOT-23-6 |  |
| 1 | U8 | Circuit intégré | TCA4307 | VSSOP-8_3x3mm_P0.65mm | tampon I2C du puck |

Non montés (empreinte prévue) : R16 0R DNP (puck : VBAT); R17 4k7 DNP (rappel SDA puck); R18 4k7 DNP (rappel SCL puck).
Pastilles du PCB, rien à acheter : TP2, TP3, TP4, TP5, TP6.

### Carte boutons (20 composants)

| Qté | Repères | Type | Valeur | Boîtier | Rôle |
|---:|---|---|---|---|---|
| 5 | SW101, SW102, SW103, SW104, SW105 | Bouton | Poussoir 12 × 12 | SW_PUSH-12mm | SW101 : BTN1 ; SW102 : BTN2 ; SW103 : BTN3 ; SW104 : BTN4 ; SW105 : BTN5 |
| 2 | C101, C103 | Condensateur | 100nF | 0805 |  |
| 1 | C102 | Condensateur | 10uF | 0805 |  |
| 1 | R102 | Résistance | 10k | 0805 |  |
| 4 | R103, R104, R105, R106 | Résistance | 150R | 0805 |  |
| 2 | D101, D102 | Diode / LED | Bicolore R/V 3mm | LED_D3.0mm-3 | D101 : PWR ; D102 : GPS |
| 1 | J101 | Connecteur | Nappe | TE_84952-6_1x06-1MP_P1.0mm_Horizontal | FFC 6 P1.0 ZIF |
| 1 | Q101 | Transistor | AO3401A | SOT-23 |  |
| 1 | U101 | Circuit intégré | SRV05-4 | SOT-23-6 |  |
| 2 | U102, U103 | Circuit intégré | PCF8574T | SOIC-16W_7.5x10.3mm_P1.27mm | U102 : boutons, 0x20 ; U103 : LED, 0x21 |

**Total : 40 composants à souder.**

## Hors schéma (à acheter avec les cartes)

<!-- manuel:debut -->
_(Tenu à jour à la main, conservé d'une génération à l'autre.)_

| Version | Qté | Article | Notes |
|---|---:|---|---|
| les deux | 1 | Nappe FFC 6 voies, pas de 1,0 mm, **type B** (contacts sur faces opposées) | entre J4 et J101 ; ~50 mm, longueur à fixer |
| les deux | 1 | Module GY-271 (QMC5883L) | sur J3, soudé à plat côté GPS, sans barrette ; optionnel |
| GPS intégré | 1 | Antenne GPS active, prise SMA | |
| GPS intégré | 1 | Pigtail U.FL → SMA femelle de cloison | de J2 à la SMA tenue par le manchon d'antenne |
| puck | 1 | Puck GPS de drone (NEO-M8N + boussole, 4 + 2 fils) | fiche à refaire en JST-PH 6 pour J6 |

La carte Waveshare ESP32-S3-Touch-LCD-3.5B, la batterie, le haut-parleur et la visserie du boîtier ne
sont pas dans cette BOM.

<!-- manuel:fin -->
